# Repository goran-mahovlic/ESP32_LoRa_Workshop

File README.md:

# Catapillar LoRa Workshop (temperary git -- will be moved once ready)

Material for Radiona LoRa workshop

https://radiona.org/radionica-sumovi-sume-lorawan-tehnologija/

Hardware for LoRa workshop

Software for LoRa workshop

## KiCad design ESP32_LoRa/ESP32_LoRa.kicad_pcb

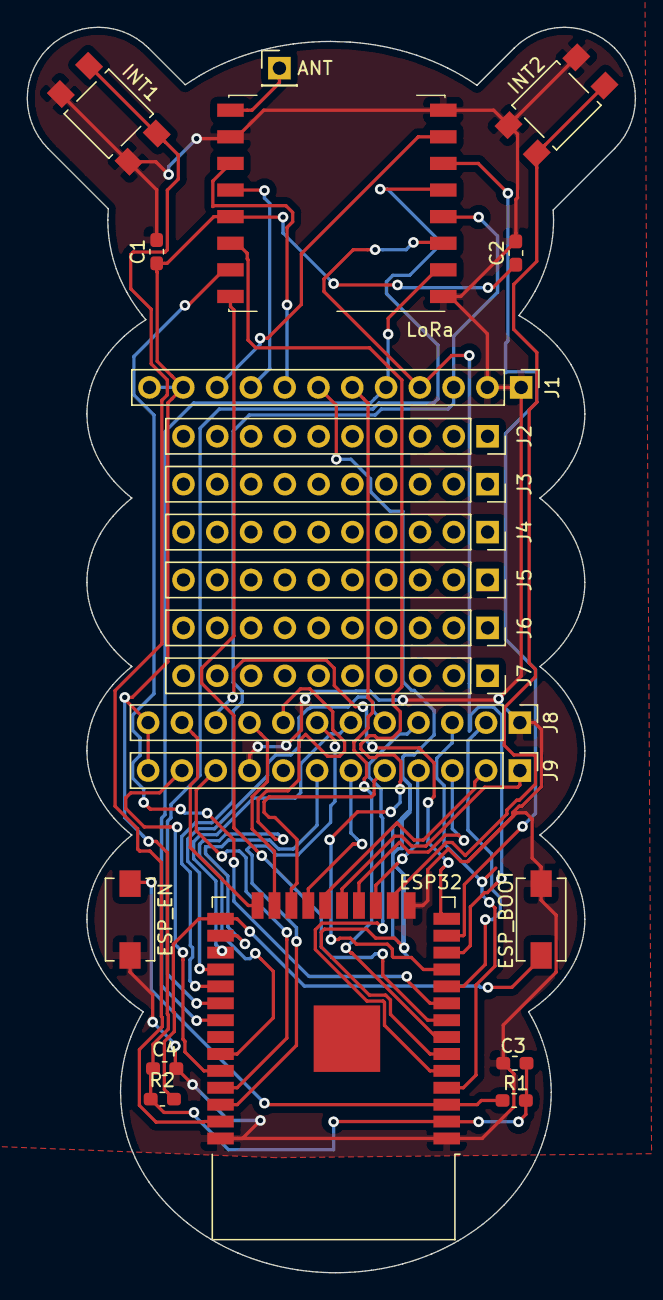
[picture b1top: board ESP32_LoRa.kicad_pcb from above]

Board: 2 copper layers, 45.7 x 93.6 mm, 22 parts (0 on the bottom side), 39 nets.

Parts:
ANT: ANT; PinHeader_1x01_P2.54mm_Vertical
C1, C2, C3, C4: C; C_0603_1608Metric_Pad1.05x0.95mm_HandSolder
ESP32: ESP32-WROOM-32
ESP_BOOT: SW_BOOT; SW_SPST_EVQPE1
ESP_EN: SW_EN; SW_SPST_EVQPE1
INT1, INT2: SW_Push; SW_SPST_TL3305A
J1, J8, J9: Conn_01x12; PinHeader_1x12_P2.54mm_Vertical
J2, J3, J4, J5, J6, J7: Conn_01x10; PinSocket_1x10_P2.54mm_Vertical
LoRa: RFM95W-868S2; HOPERF_RFM9XW_SMD
R1, R2: 10K; R_0603_1608Metric_Pad1.05x0.95mm_HandSolder

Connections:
+3V3: C1.1, C2.1, C3.1, C4.1, ESP32.2, J1.11, J1.12, J8.12, J9.12, LoRa.13, R1.1, R2.1
ESP_BOOT: ESP32.25, ESP_BOOT.1, R2.2
ESP_CLK: ESP32.20, J9.2
ESP_CMD: ESP32.19, J9.1
ESP_EN: ESP32.3, ESP_EN.1, R1.2
ESP_IO2: ESP32.24, J8.11
ESP_IO4: ESP32.26, J9.7
ESP_IO12: ESP32.14, J8.10
ESP_IO15: ESP32.23, J8.9
ESP_IO16: ESP32.27, J8.6
ESP_IO17: ESP32.28, J8.5
ESP_IO21: ESP32.33, J8.8
ESP_IO22: ESP32.36, J8.7
ESP_IO25: ESP32.10, J8.2
ESP_IO34: ESP32.6, J1.7
ESP_IO35: ESP32.7, J1.6
ESP_RX: ESP32.34, J9.11
ESP_SD0: ESP32.21, J9.6
ESP_SD1: ESP32.22, J9.5
ESP_SD2: ESP32.17, J9.4
ESP_SD3: ESP32.18, J9.3
ESP_SEND_VN: ESP32.5, J8.4
ESP_SENS_VP: ESP32.4, J8.3
ESP_TX: ESP32.35, J9.10
GND: C1.2, C2.2, C3.2, C4.2, ESP32.1, ESP32.15, ESP32.38, ESP_BOOT.2, ESP_EN.2, INT1.1, INT2.1, J1.1, J1.2, J8.1, J9.9, LoRa.1, LoRa.8, LoRa.10
INT1: ESP32.37, INT1.2
INT2: ESP32.16, INT2.2
LoRa_ANT: ANT.1, LoRa.9
LoRa_DIO0: ESP32.11, LoRa.14
LoRa_DIO1: ESP32.9, LoRa.15
LoRa_DIO2: ESP32.8, LoRa.16
LoRa_DIO3: J1.8, LoRa.11
LoRa_DIO4: J1.9, LoRa.12
LoRa_DIO5: J1.10, LoRa.7
LoRa_MISO: ESP32.31, J1.5, LoRa.2
LoRa_MOSI: ESP32.12, J1.4, LoRa.3
LoRa_NSS: ESP32.30, LoRa.5
LoRa_RST: ESP32.13, LoRa.6
LoRa_SCK: ESP32.29, J1.3, LoRa.4

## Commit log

2019-07-07 Initial version
2019-07-16 Different sorting -- Adding initial code from DonationBoxV3
2019-09-24 Adding initial picture
